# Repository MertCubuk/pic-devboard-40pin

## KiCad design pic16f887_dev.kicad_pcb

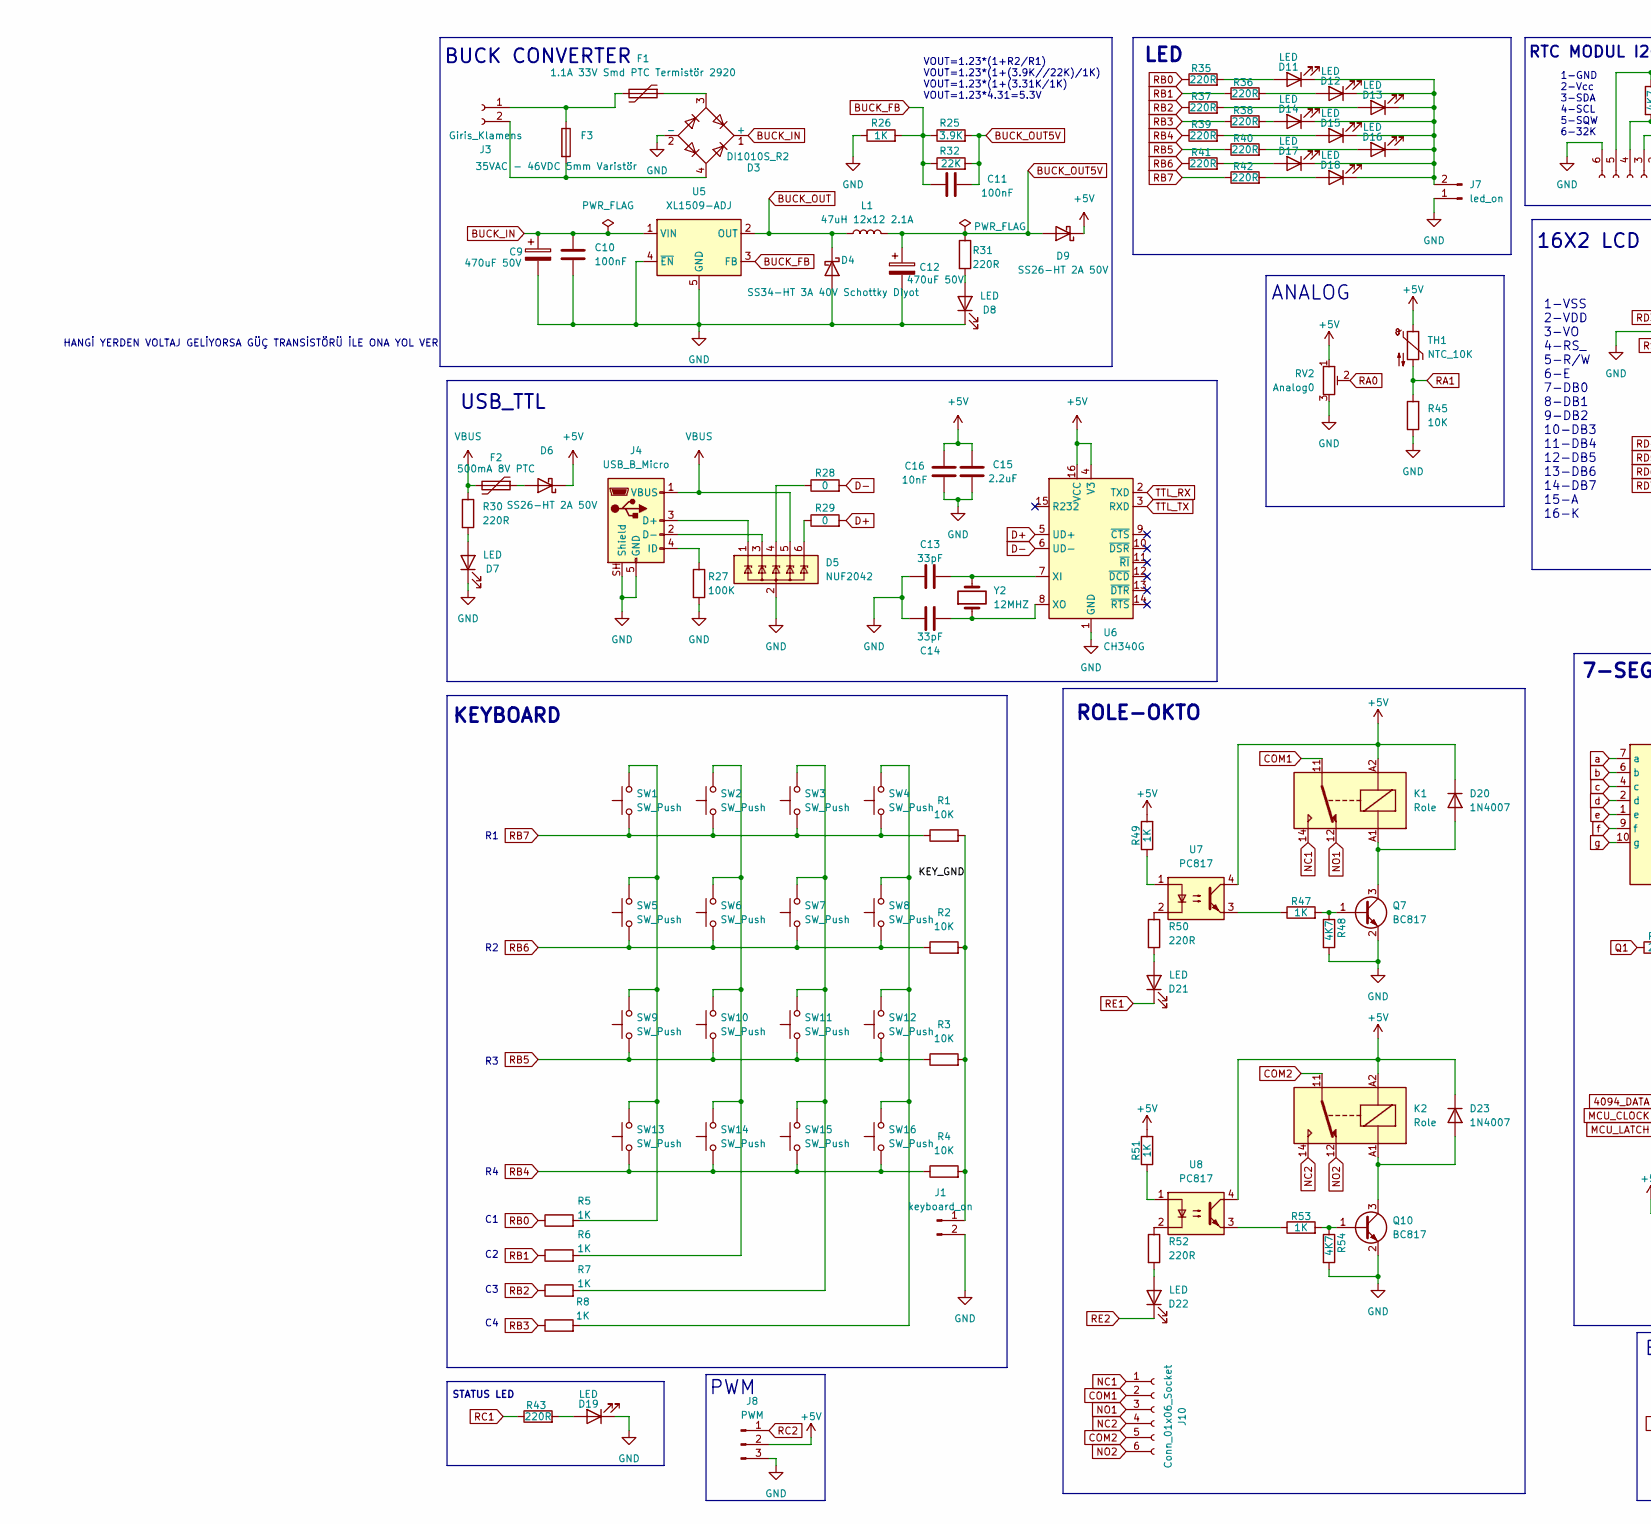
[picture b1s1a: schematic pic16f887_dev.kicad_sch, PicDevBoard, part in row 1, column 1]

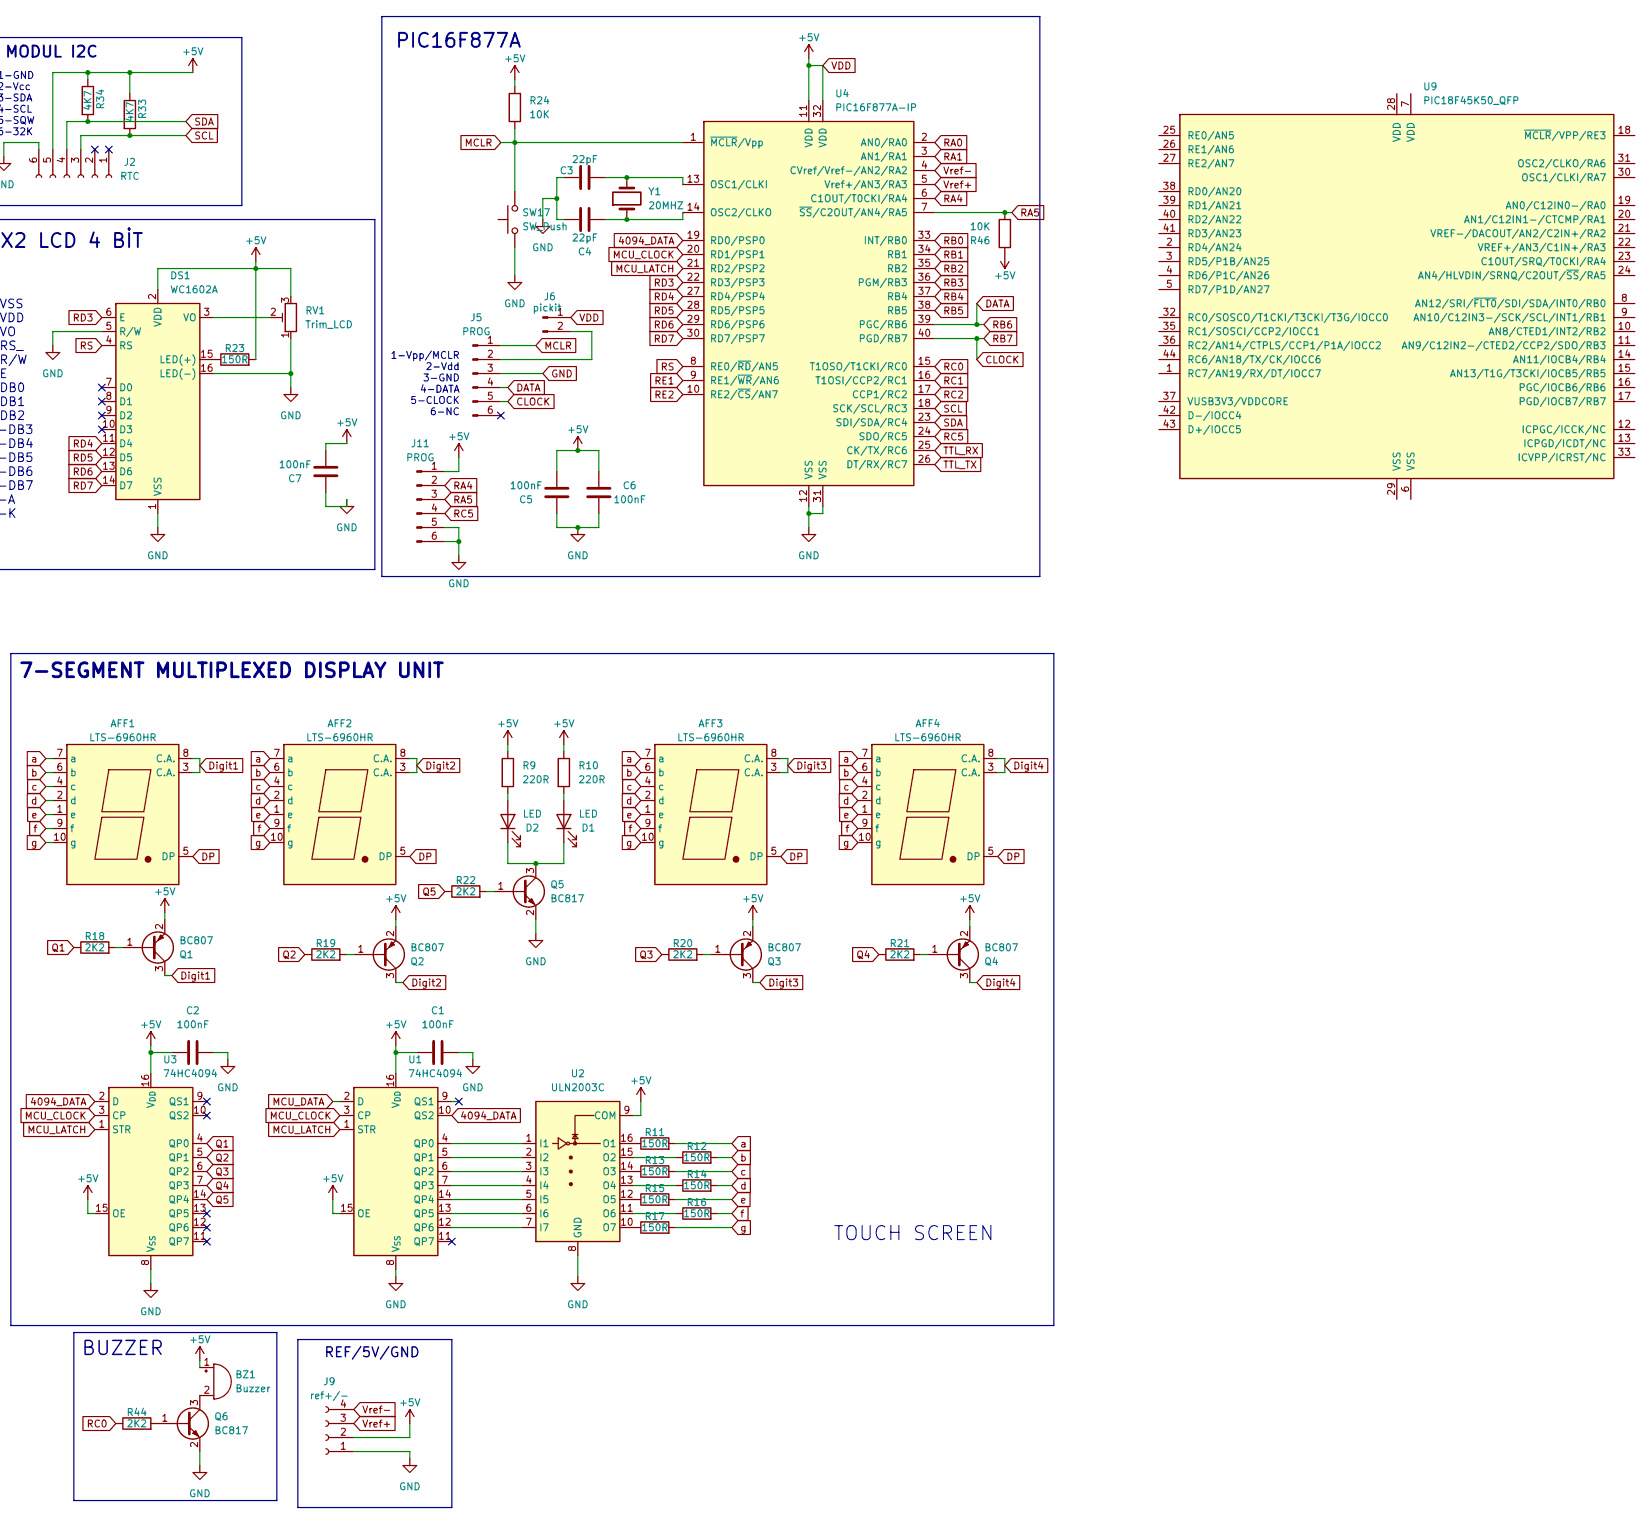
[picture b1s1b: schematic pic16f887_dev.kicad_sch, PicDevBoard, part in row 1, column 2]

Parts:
AFF1, AFF2, AFF3, AFF4: LTS-6960HR; 7SegmentLED_LTS6760_LTS6780
BZ1: Buzzer; Buzzer_12x9.5RM7.6
C1, C2, C5, C6, C7, C10, C11: 100nF; C_0805_2012Metric
C3, C4: 22pF; C_0805_2012Metric
C9, C12: 470uF 50V; CP_Radial_D10.0mm_P5.00mm
C13, C14: 33pF; C_0805_2012Metric
C15: 2.2uF; C_0603_1608Metric
C16: 10nF; C_0805_2012Metric
D1, D2: LED; LED_D5.0mm
D3: DI1010S_R2; Diode_Bridge_OnSemi_SDIP-4L
D4: SS34-HT 3A 40V Schottky Diyot; D_SMC
D5: NUF2042; SOT-563
D6, D9: SS26-HT 2A 50V; D_SMA
D7, D8, D11, D12, D13, D14, D15, D16, D17, D18, D19, D21, D22: LED; LED_0805_2012Metric
D20, D23: 1N4007; D_SMA
DS1: WC1602A
F1: 1.1A 33V Smd PTC Termistör 2920; Fuse_2920_7451Metric
F2: 500mA 8V PTC; Fuse_1206_3216Metric
F3: 35VAC - 46VDC 5mm Varistör; Fuse_BelFuse_0ZRE0100FF_L18.7mm_W5.1mm
J1: keyboard_on; PinHeader_1x02_P2.54mm_Vertical
J2: RTC; PinHeader_1x06_P2.54mm_Vertical
J3: Giris_Klamens; TerminalBlock_Phoenix_MKDS-3-2-5.08_1x02_P5.08mm_Horizontal
J4: USB_B_Micro; USB_Micro-AB_Molex_47590-0001
J5, J11: PROG; PinHeader_1x06_P2.54mm_Vertical
J6: pickit; PinHeader_1x02_P2.54mm_Vertical
J7: led_on; PinHeader_1x02_P2.54mm_Vertical
J8: PWM; JST_XH_B3B-XH-A_1x03_P2.50mm_Vertical
J9: ref+/-; PinHeader_1x04_P2.54mm_Vertical
J10: Conn_01x06_Socket; TerminalBlock_Phoenix_MKDS-3-6-5.08_1x06_P5.08mm_Horizontal
K1, K2: Role; Relay_SPDT_Finder_36.11
L1: 47uH 12x12 2.1A; L_12x12mm_H6mm
Q1, Q2, Q3, Q4: BC807; SOT-23
Q5, Q6, Q7, Q10: BC817; SOT-23
R1, R2, R3, R4, R24, R45, R46: 10K; R_0603_1608Metric
R5, R6, R7, R8, R26, R47, R49, R51, R53: 1K; R_0603_1608Metric
R9, R10, R30, R31, R35, R36, R37, R38, R39, R40, R41, R42, R43, R50, R52: 220R; R_0603_1608Metric
R11, R12, R13, R14, R15, R16, R17, R23: 150R; R_0603_1608Metric
R18, R19, R20, R21, R22, R44: 2K2; R_0603_1608Metric
R25: 3.9K; R_0805_2012Metric
R27: 100K; R_0603_1608Metric
R28, R29: 0; R_0603_1608Metric
R32: 22K; R_0603_1608Metric
R33, R34, R48, R54: 4K7; R_0603_1608Metric
RV1: Trim_LCD; Potentiometer_Bourns_3296W_Vertical
RV2: Analog0; Potentiometer_Piher_PT-10-V10_Vertical_Hole
SW1, SW2, SW3, SW4, SW5, SW6, SW7, SW8, SW9, SW10, SW11, SW12, SW13, SW14, SW15, SW16, SW17: SW_Push; SW_PUSH_6mm_H5mm
TH1: NTC_10K; R_Axial_DIN0204_L3.6mm_D1.6mm_P1.90mm_Vertical
U1, U3: 74HC4094; SOIC-16_3.9x9.9mm_P1.27mm
U2: ULN2003C; SOP-16_4.4x10.4mm_P1.27mm
U4: PIC16F877A-IP; DIP-40_W15.24mm
U5: XL1509-ADJ; SOP-8_3.76x4.96mm_P1.27mm
U6: CH340G; SOIC-16_3.9x9.9mm_P1.27mm
U7, U8: PC817; DIP-4_W7.62mm
U9: PIC18F45K50_QFP; TQFP-44_10x10mm_P0.8mm
Y1: 20MHZ; Crystal_SMD_HC49-SD
Y2: 12MHZ; Crystal_SMD_HC49-SD

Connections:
4094_DATA: U1.10 (QS2), U3.2 (D), U4.19 (RD0/PSP0)
/KEY_GND: J1.1, R1.2, R2.2, R3.2, R4.2
BUCK_FB: C11.1, R25.1, R26.2, R32.1, U5.3 (FB)
BUCK_IN: C9.1, C10.1, D3.1 (+), U5.1 (VIN)
BUCK_OUT: D4.1 (K), L1.1, U5.2 (OUT)
BUCK_OUT5V: C11.2, C12.1, D9.2 (A), L1.2, R25.2, R31.1, R32.2
CLOCK: J5.5, R1.1, R42.1, SW1.1, SW2.1, SW3.1, SW4.1, U4.40 (PGD/RB7)
COM1: J10.2, K1.11
COM2: J10.5, K2.11
D+: R29.2, U6.5 (UD+)
D-: R28.2, U6.6 (UD-)
DATA: J5.4, R2.1, R41.1, SW5.1, SW6.1, SW7.1, SW8.1, U4.39 (PGC/RB6)
DP: AFF1.5 (DP), AFF2.5 (DP), AFF3.5 (DP), AFF4.5 (DP)
Digit1: AFF1.3 (C.A.), AFF1.8 (C.A.), Q1.3 (C)
Digit2: AFF2.3 (C.A.), AFF2.8 (C.A.), Q2.3 (C)
Digit3: AFF3.3 (C.A.), AFF3.8 (C.A.), Q3.3 (C)
Digit4: AFF4.3 (C.A.), AFF4.8 (C.A.), Q4.3 (C)
GND: C1.2, C2.2, C3.1, C4.2, C5.2, C6.1, C7.2, C9.2, C10.2, C12.2, C13.1, C14.2, C15.1, C16.1, D3.2 (-), D4.2 (A), D5.2 (GND), D7.1 (K), D8.1 (K), D19.1 (K), DS1.1 (VSS), DS1.5 (R/W), DS1.16 (LED(-)), J1.2, J2.6, J4.5 (GND), J4.SH (Shield), J5.3, J7.1, J8.3, J9.1, J11.5, J11.6, Q5.2 (E), Q6.2 (E), Q7.2 (E), Q10.2 (E), R26.1, R27.2, R45.1, R48.2, R54.2, RV1.1, RV2.3, SW17.1, U1.8 (V_{SS}), U2.8 (GND), U3.8 (V_{SS}), U4.12 (VSS), U4.31 (VSS), U5.4 (~EN), U5.5 (GND), U5.6 (GND), U5.7 (GND), U5.8 (GND), U6.1 (GND)
MCLR: J5.1, R24.1, SW17.2, U4.1 (~MCLR/Vpp)
MCU_CLOCK: U1.3 (CP), U3.3 (CP), U4.20 (RD1/PSP1)
MCU_DATA: U1.2 (D)
MCU_LATCH: U1.1 (STR), U3.1 (STR), U4.21 (RD2/PSP2)
NC1: J10.1, K1.14
NC2: J10.4, K2.14
NO1: J10.3, K1.12
NO2: J10.6, K2.12
unnamed: BZ1.2 (-), Q6.3 (C)
unnamed: D1.2 (A), R10.2
unnamed: D1.1 (K), D2.1 (K), Q5.3 (C)
unnamed: D2.2 (A), R9.2
unnamed: D3.3, F1.1
unnamed: D5.1 (IO1), J4.3 (D+)
unnamed: D5.3 (IO2), J4.2 (D-)
unnamed: D5.4 (IO3), R28.1
unnamed: D5.6 (IO5), R29.1
unnamed: D6.2 (A), F2.1
unnamed: D7.2 (A), R30.2
unnamed: D8.2 (A), R31.2
unnamed: D11.2 (A), R35.2
unnamed: D11.1 (K), D12.1 (K), D13.1 (K), D14.1 (K), D15.1 (K), D16.1 (K), D17.1 (K), D18.1 (K), J7.2
unnamed: D12.2 (A), R36.2
unnamed: D13.2 (A), R37.2
unnamed: D14.2 (A), R38.2
unnamed: D15.2 (A), R39.2
unnamed: D16.2 (A), R40.2
unnamed: D17.2 (A), R41.2
unnamed: D18.2 (A), R42.2
unnamed: D19.2 (A), R43.2
unnamed: D20.2 (A), K1.A1, Q7.3 (C)
unnamed: D21.2 (A), R50.2
unnamed: D22.2 (A), R52.2
unnamed: D23.2 (A), K2.A1, Q10.3 (C)
unnamed: DS1.15 (LED(+)), R23.1
unnamed: DS1.3 (VO), RV1.2
unnamed: F1.2, F3.1, J3.1
unnamed: D3.4, F3.2, J3.2
unnamed: J4.4 (ID), R27.1
unnamed: J5.2, J6.2
unnamed: Q1.1 (B), R18.2
unnamed: Q2.1 (B), R19.2
unnamed: Q3.1 (B), R20.2
unnamed: Q4.1 (B), R21.2
unnamed: Q5.1 (B), R22.2
unnamed: Q6.1 (B), R44.2
unnamed: Q7.1 (B), R47.2, R48.1
unnamed: Q10.1 (B), R53.2, R54.1
unnamed: R5.2, SW1.2, SW5.2, SW9.2, SW13.2
unnamed: R6.2, SW2.2, SW6.2, SW10.2, SW14.2
unnamed: R7.2, SW3.2, SW7.2, SW11.2, SW15.2
unnamed: R8.2, SW4.2, SW8.2, SW12.2, SW16.2
unnamed: R47.1, U7.3
unnamed: R49.1, U7.1
unnamed: R50.1, U7.2
unnamed: R51.1, U8.1
unnamed: R52.1, U8.2
unnamed: R53.1, U8.3
unnamed: U1.4 (QP0), U2.1 (I1)
unnamed: U1.5 (QP1), U2.2 (I2)
unnamed: U1.6 (QP2), U2.3 (I3)
unnamed: U1.7 (QP3), U2.4 (I4)
unnamed: U1.14 (QP4), U2.5 (I5)
unnamed: U1.13 (QP5), U2.6 (I6)
unnamed: U1.12 (QP6), U2.7 (I7)
unnamed: R11.1, U2.16 (O1)
unnamed: R12.1, U2.15 (O2)
unnamed: R13.1, U2.14 (O3)
unnamed: R14.1, U2.13 (O4)
unnamed: R15.1, U2.12 (O5)
unnamed: R16.1, U2.11 (O6)
unnamed: R17.1, U2.10 (O7)
unnamed: C3.2, U4.13 (OSC1/CLKI), Y1.2
unnamed: C4.1, U4.14 (OSC2/CLKO), Y1.1
unnamed: C13.2, U6.7 (XI), Y2.2
unnamed: C14.1, U6.8 (XO), Y2.1
Q1: R18.1, U3.4 (QP0)
Q2: R19.1, U3.5 (QP1)
Q3: R20.1, U3.6 (QP2)
Q4: R21.1, U3.7 (QP3)
Q5: R22.1, U3.14 (QP4)
RA0: RV2.2, U4.2 (AN0/RA0)
RA1: R45.2, TH1.2, U4.3 (AN1/RA1)
RA4: J11.2, U4.6 (C1OUT/T0CKI/RA4)
RA5: J11.3, R46.2, U4.7 (~SS/C2OUT/AN4/RA5)
RB0: R5.1, R35.1, U4.33 (INT/RB0)
RB1: R6.1, R36.1, U4.34 (RB1)
RB2: R7.1, R37.1, U4.35 (RB2)
RB3: R8.1, R38.1, U4.36 (PGM/RB3)
RB4: R4.1, R39.1, SW13.1, SW14.1, SW15.1, SW16.1, U4.37 (RB4)
RB5: R3.1, R40.1, SW9.1, SW10.1, SW11.1, SW12.1, U4.38 (RB5)
RC0: R44.1, U4.15 (T1OSO/T1CKI/RC0)
RC1: R43.1, U4.16 (T1OSI/CCP2/RC1)
RC2: J8.1, U4.17 (CCP1/RC2)
RC5: J11.4, U4.24 (SDO/RC5)
RD3: DS1.6 (E), U4.22 (RD3/PSP3)
RD4: DS1.11 (D4), U4.27 (RD4/PSP4)
RD5: DS1.12 (D5), U4.28 (RD5/PSP5)
RD6: DS1.13 (D6), U4.29 (RD6/PSP6)
RD7: DS1.14 (D7), U4.30 (RD7/PSP7)
RE1: D21.1 (K), U4.9 (RE1/~WR/AN6)
RE2: D22.1 (K), U4.10 (RE2/~CS/AN7)
RS: DS1.4 (RS), U4.8 (RE0/~RD/AN5)
SCL: J2.3, R33.2, U4.18 (SCK/SCL/RC3)
SDA: J2.4, R34.2, U4.23 (SDI/SDA/RC4)
TTL_RX: U4.25 (CK/TX/RC6), U6.2 (TXD)
TTL_TX: U4.26 (DT/RX/RC7), U6.3 (RXD)
VBUS: D5.5 (IO4), F2.2, J4.1 (VBUS), R30.1
VDD: BZ1.1 (+), C1.1, C2.1, C5.1, C6.2, C7.1, C15.2, C16.2, D6.1 (K), D9.1 (K), D20.1 (K), D23.1 (K), DS1.2 (VDD), J2.5, J6.1, J8.2, J9.2, J11.1, K1.A2, K2.A2, Q1.2 (E), Q2.2 (E), Q3.2 (E), Q4.2 (E), R9.1, R10.1, R23.2, R24.2, R33.1, R34.1, R46.1, R49.2, R51.2, RV1.3, RV2.1, TH1.1, U1.15 (OE), U1.16 (V_{DD}), U2.9 (COM), U3.15 (OE), U3.16 (V_{DD}), U4.11 (VDD), U4.32 (VDD), U6.4 (V3), U6.16 (VCC), U7.4, U8.4
Vref+: J9.3, U4.5 (Vref+/AN3/RA3)
Vref-: J9.4, U4.4 (CVref/Vref-/AN2/RA2)
a: AFF1.7 (a), AFF2.7 (a), AFF3.7 (a), AFF4.7 (a), R11.2
b: AFF1.6 (b), AFF2.6 (b), AFF3.6 (b), AFF4.6 (b), R12.2
c: AFF1.4 (c), AFF2.4 (c), AFF3.4 (c), AFF4.4 (c), R13.2
d: AFF1.2 (d), AFF2.2 (d), AFF3.2 (d), AFF4.2 (d), R14.2
e: AFF1.1 (e), AFF2.1 (e), AFF3.1 (e), AFF4.1 (e), R15.2
f: AFF1.9 (f), AFF2.9 (f), AFF3.9 (f), AFF4.9 (f), R16.2
g: AFF1.10 (g), AFF2.10 (g), AFF3.10 (g), AFF4.10 (g), R17.2

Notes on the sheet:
STATUS LED
ANALOG
16X2 LCD 4 BİT
BUZZER
1-GND 2-Vcc 3-SDA 4-SCL 5-SQW 6-32K
1-Vpp/MCLR 2-Vdd 3-GND 4-DATA 5-CLOCK 6-NC
VOUT=1.23*(1+R2/R1) VOUT=1.23*(1+(3.9K//22K)/1K) VOUT=1.23*(1+(3.31K/1K) VOUT=1.23*4.31=5.3V
1-VSS 2-VDD 3-VO 4-RS_ 5-R/W 6-E 7-DB0 8-DB1 9-DB2 10-DB3 11-DB4 12-DB5 13-DB6 14-DB7 15-A 16-K
HANGİ YERDEN VOLTAJ GELİYORSA GÜÇ TRANSİSTÖRÜ İLE ONA YOL VER
KEYBOARD
PWM
7-SEGMENT MULTIPLEXED DISPLAY UNIT
BUCK CONVERTER
REF/5V/GND
RTC MODUL I2C
ROLE-OKTO
USB_TTL
LED
PIC16F877A
TOUCH SCREEN

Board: 2 copper layers, 153 parts (6 on the bottom side), 135 nets, no tracks yet.

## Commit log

2026-04-21 Initial commit: PIC devboard V0.10
